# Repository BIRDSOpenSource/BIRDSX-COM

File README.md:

<div align="center">
  
</div> 

<div align="center">
  
</div>

## BIRDSX-COM
Documentaion and CAD files for Antenna Panel in Dragonfly Satellite.

## About the BIRDSX Program:

The Mission Statement of the Project is:

> “The goal of our project is to bring diversity to the space sector and democratize the usage of space.”

The project is led by Kyushu Institute of Technology in Japan and involves students from France, Mexico, Nepal, Thailand, Vietnam, Paraguay and Japan.

Satellite Names: Dragonfly (Japan), 

Stakeholders:  Our stakeholders are Kyushu Institute of Technology (Kyutech) and the Association for Radio Digital Communications (ARDC).

Project duration: 2023-2024

CubeSat: 2U (20x10x10) cm3

Weight: 1.13kg

Launch Date: 21st February 2025

BIRDS-X project is a 2U CubeSat dedicated to amateur radio communication.

## Organisation structure

```bash

```

## Features

## I like this project, can I help you?
You are welcome 🙂

* Give us a star ⭐
* Watch repository to be notified about updates 👀
* If you will find some errors, report them in Issues 🐞
* Try Birds designs on some real computer and let us know how it worked in Discussions. 💬
* We would greatly appreciate if you would also tell others about this ecosystem, it helps us to improve BIRDS Open Source. Thank you!

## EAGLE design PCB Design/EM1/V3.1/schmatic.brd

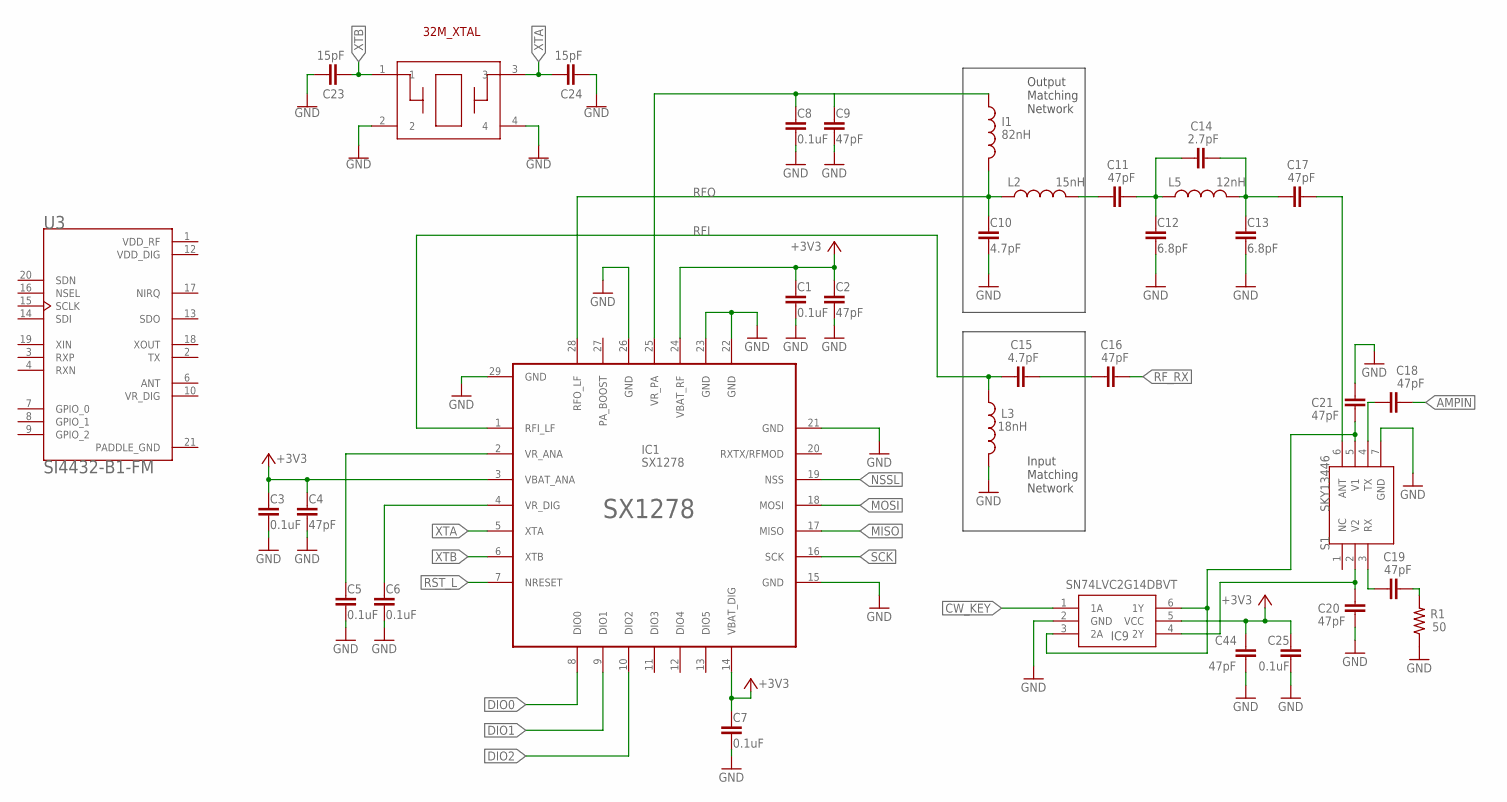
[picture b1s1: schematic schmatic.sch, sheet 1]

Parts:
C1, C3, C5, C6, C7, C8, C25: 0.1uF; M(1005)_US(0402)
C2, C4, C9, C11, C16, C17, C18, C19, C20, C21, C44: 47pF; M(1005)_US(0402)
C10, C15: 4.7pF; M(1005)_US(0402)
C12, C13: 6.8pF; M(1005)_US(0402)
C14: 2.7pF; M(1005)_US(0402)
C23, C24: 15pF; CAP_(M1005)_0402
I1: 82nH; M(1608)_US(0603)
IC1: SX1278
IC9: SN74LVC2G14DBVT; SOT-23-6
L2: 15nH; M(1005)_US(0402)
L3: 18nH; M(1005)_US(0402)
L5: 12nH; M(1005)_US(0402)
Q1: NX2520SA-32MHZ; NX2520SA
R1: 50; M(1608)_US(0603)
S1: SKY13446
U3: SI4432-B1-FM; QFN50P400X400X90-21N

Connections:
+3V1: C5.1, IC1.2 (VR_ANA)
+3V2: C6.1, IC1.4 (VR_DIG)
+3V3: C1.1, C2.1, C3.1, C4.1, C7.1, C25.1, C44.1, IC1.3 (VBAT_ANA), IC1.14 (VBAT_DIG), IC1.24 (VBAT_RF), IC9.5 (VCC); also elsewhere on the board
+3V4: C8.1, C9.1, I1.1, IC1.25 (VR_PA)
AMPIN: C18.2; also elsewhere on the board
CW_KEY: IC9.1 (1A); also elsewhere on the board
DIO0: IC1.8 (DIO0); also elsewhere on the board
DIO1: IC1.9 (DIO1); also elsewhere on the board
DIO2: IC1.10 (DIO2); also elsewhere on the board
GND: C1.2, C2.2, C3.2, C4.2, C5.2, C6.2, C7.2, C8.2, C9.2, C10.2, C12.2, C13.2, C20.1, C21.2, C23.1, C24.2, C25.2, C44.2, IC1.15 (GND), IC1.21 (GND), IC1.22 (GND), IC1.23 (GND), IC1.26 (GND), IC1.29 (GND), IC9.2 (GND), L3.2, Q1.2, Q1.4, R1.1, S1.7 (GND); also elsewhere on the board
MISO: IC1.17 (MISO); also elsewhere on the board
MOSI: IC1.18 (MOSI); also elsewhere on the board
unnamed: C11.1, L2.2
unnamed: C11.2, C12.1, C14.1, L5.1
unnamed: C13.1, C14.2, C17.1, L5.2
unnamed: C17.2, S1.6 (ANT)
unnamed: C15.2, C16.1
unnamed: C18.1, S1.4 (TX)
unnamed: C19.1, S1.3 (RX)
unnamed: C19.2, R1.2
unnamed: C20.2, IC9.4 (2Y), S1.2 (V2)
unnamed: C21.1, IC9.3 (2A), IC9.6 (1Y), S1.5 (V1)
NSSL: IC1.19 (NSS); also elsewhere on the board
RFI: C15.1, IC1.1 (RFI_LF), L3.1
RFO: C10.1, I1.2, IC1.28 (RFO_LF), L2.1
RF_RX: C16.2; also elsewhere on the board
RST_L: IC1.7 (NRESET); also elsewhere on the board
SCK: IC1.16 (SCK); also elsewhere on the board
VDD_DIG: U3.12 (VDD_DIG)
VDD_RF: U3.1 (VDD_RF)
XTA: C24.1, IC1.5 (XTA), Q1.3
XTB: C23.2, IC1.6 (XTB), Q1.1

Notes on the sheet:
Output Matching Network
Input Matching Network
32M_XTAL

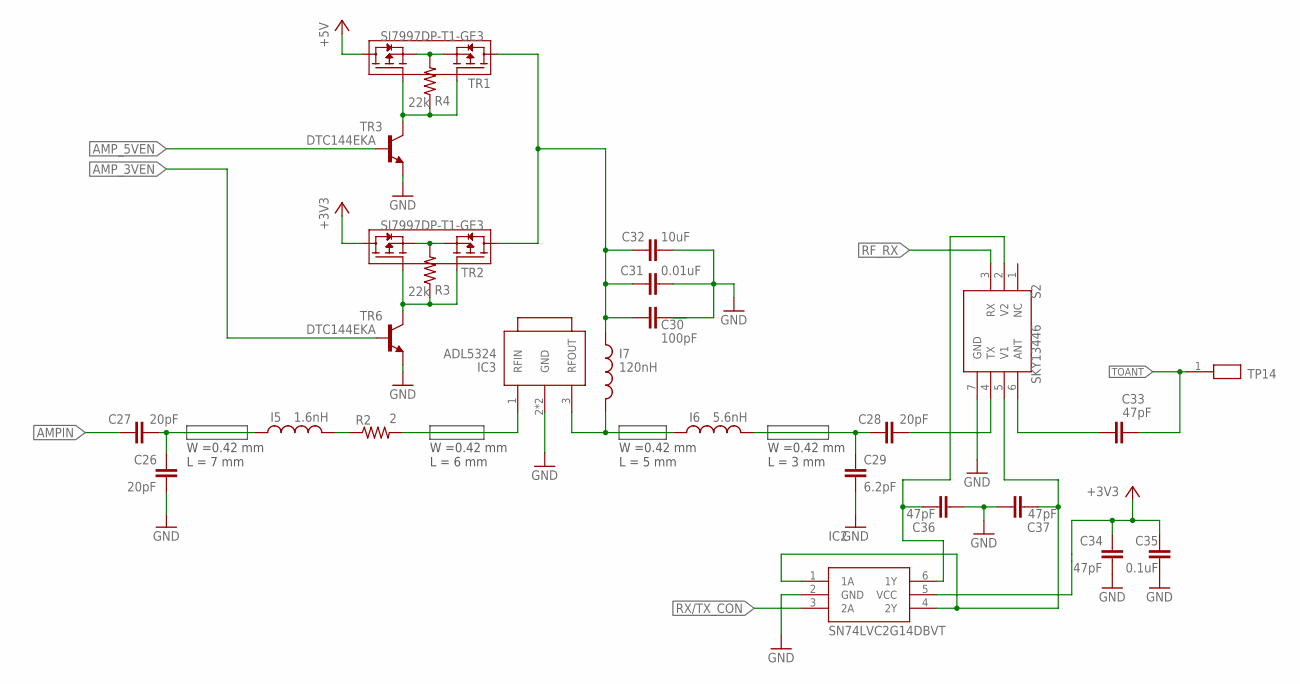
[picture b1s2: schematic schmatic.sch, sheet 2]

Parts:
C26, C27, C28: 20pF; M(1005)_US(0402)
C29: 6.2pF; M(1005)_US(0402)
C30: 100pF; M(1005)_US(0402)
C31: 0.01uF; M(1005)_US(0402)
C32: 10uF; M(1608)_US(0603)
C33, C34, C36, C37: 47pF; M(1005)_US(0402)
C35: 0.1uF; M(1005)_US(0402)
I5: 1.6nH; M(1005)_US(0402)
I6: 5.6nH; M(1005)_US(0402)
I7: 120nH; M(2012)_US(0805)
IC2: SN74LVC2G14DBVT; SOT-23-6
IC3: ADL5324
R2: 2; M(1608)_US(0603)
R3, R4: 22k; M(1608)_US(0603)
S2: SKY13446
TP14: TEST_POINT; TEST_POINT_1.5MM
TR1, TR2: SI7997DP-T1-GE3
TR3, TR6: DTC144EKA; SOT346-R

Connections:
+3V3: C34.1, C35.1, IC2.5 (VCC), TR2.7 (D1), TR2.8 (D1), TR2.10 (D1); also elsewhere on the board
+3V5: C30.1
+5V: TR1.7 (D1), TR1.8 (D1), TR1.10 (D1); also elsewhere on the board
AMPIN: C27.1; also elsewhere on the board
AMPPWR: C30.2, C31.2, C32.1, I7.1, TR1.5 (D2), TR1.6 (D2), TR1.9 (D2), TR2.5 (D2), TR2.6 (D2), TR2.9 (D2)
AMP_3VEN: TR6.2 (B); also elsewhere on the board
AMP_5VEN: TR3.2 (B); also elsewhere on the board
GND: C26.2, C29.2, C31.1, C32.2, C34.2, C35.2, C36.1, C37.2, IC2.2 (GND), IC3.2 (GND), IC3.4 (GND), S2.7 (GND), TR3.1 (E), TR6.1 (E); also elsewhere on the board
unnamed: C26.1, C27.2, I5.1
unnamed: C37.1, IC2.1 (1A), IC2.4 (2Y), S2.5 (V1)
unnamed: I5.2, R2.1
unnamed: IC3.1 (RFIN), R2.2
unnamed: I6.1, I7.2, IC3.3 (RFOUT)
unnamed: C28.1, C29.1, I6.2
unnamed: C28.2, S2.4 (TX)
unnamed: C33.1, S2.6 (ANT)
unnamed: R4.2, TR1.1 (S1), TR1.3 (S2)
unnamed: R3.2, TR2.1 (S1), TR2.3 (S2)
unnamed: C36.2, IC2.6 (1Y), S2.2 (V2)
unnamed: R4.1, TR1.2 (G1), TR1.4 (G2), TR3.3 (C)
unnamed: R3.1, TR2.2 (G1), TR2.4 (G2), TR6.3 (C)
RF_RX: S2.3 (RX); also elsewhere on the board
RX/TX_CON: IC2.3 (2A); also elsewhere on the board
TOANT: C33.2, TP14.1

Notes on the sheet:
W =0.42 mm L = 3 mm
W =0.42 mm L = 5 mm
W =0.42 mm L = 6 mm
W =0.42 mm L = 7 mm

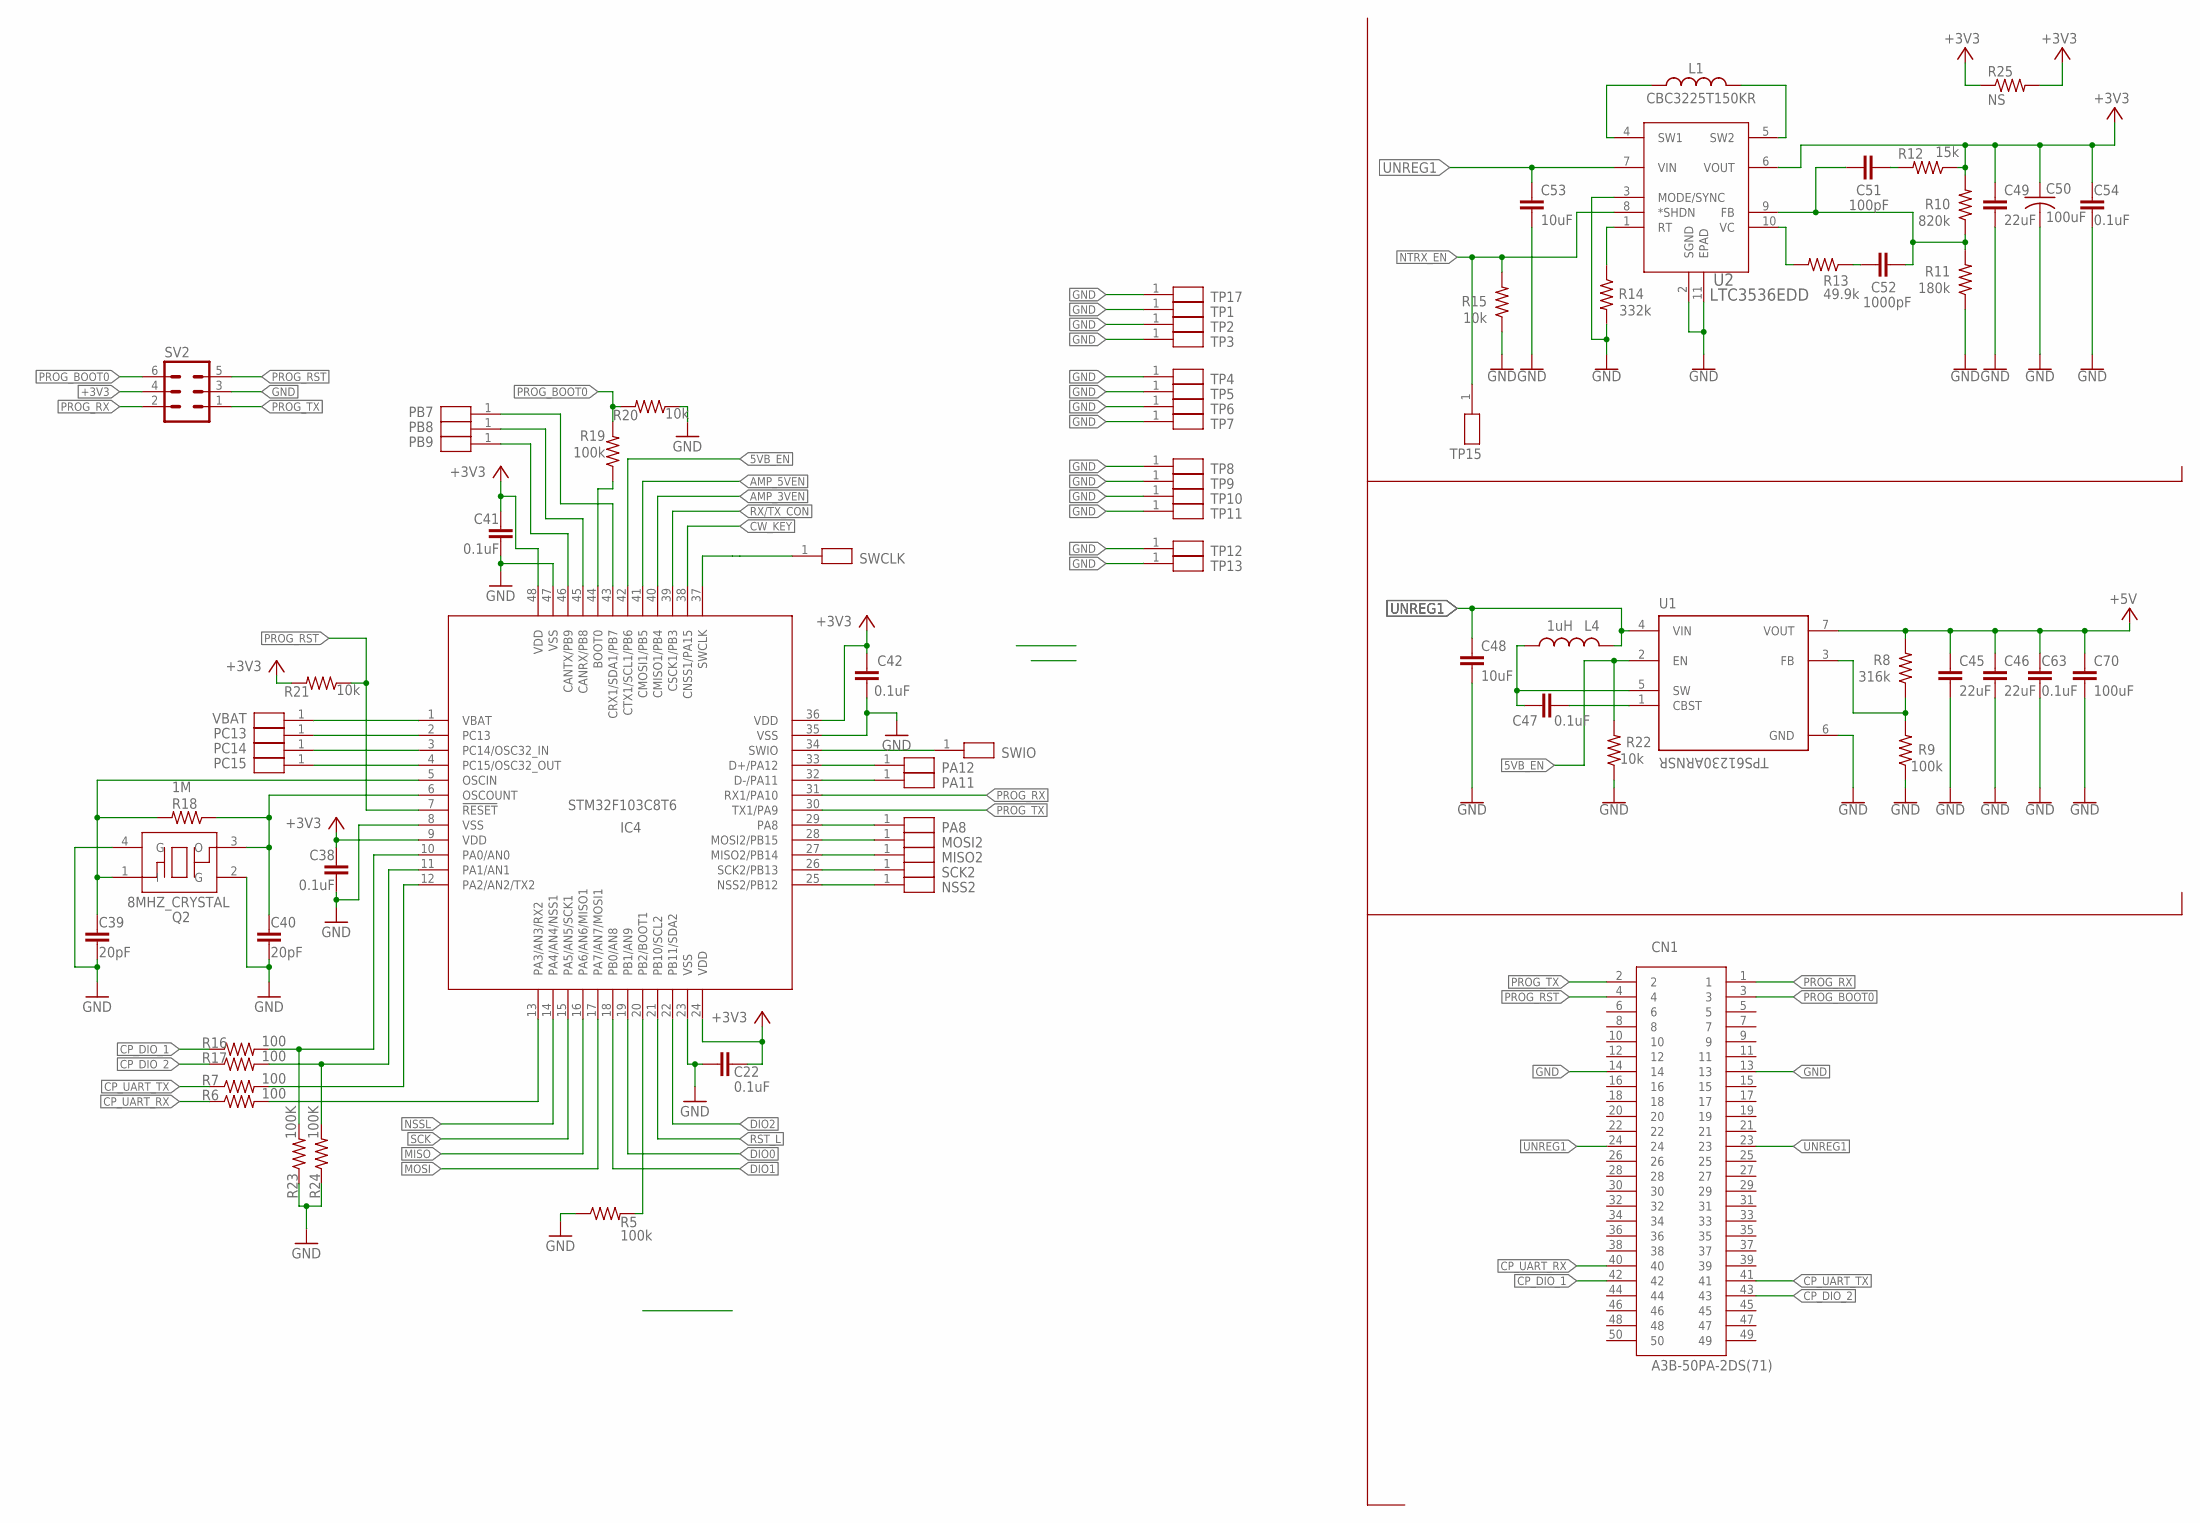
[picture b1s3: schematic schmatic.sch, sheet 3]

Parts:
C22, C38, C41, C42, C47, C54, C63: 0.1uF; M(1005)_US(0402)
C39, C40: 20pF; M(1005)_US(0402)
C45, C46, C49: 22uF; M(1608)_US(0603)
C48, C53: 10uF; M(1608)_US(0603)
C50: 100uF; C1210
C51: 100pF; M(1005)_US(0402)
C52: 1000pF; M(1005)_US(0402)
C70: 100uF; M(2012)_US(0805)
CN1: A3B-50PA-2DS(71)
IC4: STM32F103C8T6
L1: CBC3225T150KR; M(3225)_US(1210)
L4: 1uH; AMDLA3020S-1R5MT
MISO2: TEST_POINT; TEST_POINT_1.5MM
MOSI2: TEST_POINT; TEST_POINT_1.5MM
NSS2: TEST_POINT; TEST_POINT_1.5MM
PA8, PA11, PA12: TEST_POINT; TEST_POINT_1.5MM
PB7, PB8, PB9: TEST_POINT; TEST_POINT_1.5MM
PC13, PC14, PC15: TEST_POINT; TEST_POINT_1.5MM
Q2: 8MHZ_CRYSTAL; ECS-80-18-30B-JEM-TR
R5, R19: 100k; M(1005)_US(0402)
R6, R7, R16, R17: 100; M(1005)_US(0402)
R8: 316k; M(1608)_US(0603)
R9: 100k; M(1608)_US(0603)
R10: 820k; M(1608)_US(0603)
R11: 180k; M(1608)_US(0603)
R12: 15k; M(1608)_US(0603)
R13: 49.9k; M(1608)_US(0603)
R14: 332k; M(1608)_US(0603)
R15, R20, R21, R22: 10k; M(1005)_US(0402)
R18: 1M; M(1608)_US(0603)
R23, R24: 100K; M(1005)_US(0402)
R25: NS; M(2012)_US(0805)
SCK2: TEST_POINT; TEST_POINT_1.5MM
SV2: MA03-2
SWCLK: TEST_POINT; TEST_POINT_1.5MM
SWIO: TEST_POINT; TEST_POINT_1.5MM
TP1, TP2, TP3, TP4, TP5, TP6, TP7, TP8, TP9, TP10, TP11, TP12, TP13, TP15, TP17: TEST_POINT; TEST_POINT_1.5MM
U1: TPS61230ARNSR; IC_TPS61230ARNSR
U2: LTC3536EDD; DFN-10_DD
VBAT: TEST_POINT; TEST_POINT_1.5MM

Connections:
5VB_EN: IC4.42 (CTX1/SCL1/PB6), R22.2, U1.2 (EN)
+3V3: C22.1, C38.1, C41.1, C42.1, C49.1, C50.1, C54.1, IC4.9 (VDD), IC4.24 (VDD), IC4.36 (VDD), IC4.48 (VDD), R10.2, R12.1, R21.2, R25.1, R25.2, SV2.4, U2.6 (VOUT); also elsewhere on the board
+5V: C45.1, C46.1, C63.1, C70.1, R8.2, U1.7 (VOUT); also elsewhere on the board
AMP_3VEN: IC4.40 (CMISO1/PB4); also elsewhere on the board
AMP_5VEN: IC4.41 (CMOSI1/PB5); also elsewhere on the board
CP_DIO_1: CN1.42, R16.1
CP_DIO_2: CN1.43, R17.1
CP_UART_RX: CN1.40, R6.1
CP_UART_TX: CN1.41, R7.1
CW_KEY: IC4.38 (CNSS1/PA15); also elsewhere on the board
C_UART_RX: IC4.13 (PA3/AN3/RX2), R6.2
C_UART_TX: IC4.12 (PA2/AN2/TX2), R7.2
DIO0: IC4.19 (PB1/AN9); also elsewhere on the board
DIO1: IC4.18 (PB0/AN8); also elsewhere on the board
DIO2: IC4.22 (PB11/SDA2); also elsewhere on the board
GND: C22.2, C38.2, C39.2, C40.2, C41.2, C42.2, C45.2, C46.2, C48.2, C49.2, C50.2, C53.2, C54.2, C63.2, C70.2, CN1.13, CN1.14, IC4.8 (VSS), IC4.23 (VSS), IC4.35 (VSS), IC4.47 (VSS), Q2.2 (G), Q2.4 (G), R5.1, R9.1, R11.1, R14.2, R15.1, R20.1, R22.1, R23.1, R24.1, SV2.3, TP1.1, TP2.1, TP3.1, TP4.1, TP5.1, TP6.1, TP7.1, TP8.1, TP9.1, TP10.1, TP11.1, TP12.1, TP13.1, TP17.1, U1.6 (GND), U2.2 (SGND), U2.3 (MODE/SYNC), U2.11 (EPAD); also elsewhere on the board
MISO: IC4.16 (PA6/AN6/MISO1); also elsewhere on the board
MOSI: IC4.17 (PA7/AN7/MOSI1); also elsewhere on the board
unnamed: IC4.10 (PA0/AN0), R16.2, R23.2
unnamed: IC4.20 (PB2/BOOT1), R5.2
unnamed: IC4.11 (PA1/AN1), R17.2, R24.2
unnamed: C39.1, IC4.5 (OSCIN), Q2.1 (I), R18.2
unnamed: C40.1, IC4.6 (OSCOUNT), Q2.3 (O), R18.1
unnamed: L1.1, U2.4 (SW1)
unnamed: R8.1, R9.2, U1.3 (FB)
unnamed: C47.1, L4.1, U1.5 (SW)
unnamed: L1.2, U2.5 (SW2)
unnamed: C47.2, U1.1 (CBST)
unnamed: IC4.1 (VBAT), VBAT.1
unnamed: C51.2, R12.2
unnamed: C51.1, C52.2, R10.1, R11.2, U2.9 (FB)
unnamed: IC4.44 (BOOT0), R19.1
unnamed: C52.1, R13.1
unnamed: R13.2, U2.10 (VC)
unnamed: R14.1, U2.1 (RT)
unnamed: IC4.4 (PC15/OSC32_OUT), PC15.1
unnamed: IC4.3 (PC14/OSC32_IN), PC14.1
unnamed: IC4.2 (PC13), PC13.1
unnamed: IC4.27 (MISO2/PB14), MISO2.1
unnamed: IC4.28 (MOSI2/PB15), MOSI2.1
unnamed: IC4.33 (D+/PA12), PA12.1
unnamed: IC4.32 (D-/PA11), PA11.1
unnamed: IC4.29 (PA8), PA8.1
unnamed: IC4.26 (SCK2/PB13), SCK2.1
unnamed: IC4.25 (NSS2/PB12), NSS2.1
NSSL: IC4.14 (PA4/AN4/NSS1); also elsewhere on the board
NTRX_EN: R15.2, TP15.1, U2.8 (*SHDN)
PB7: IC4.43 (CRX1/SDA1/PB7), PB7.1
PB8: IC4.45 (CANRX/PB8), PB8.1
PB9: IC4.46 (CANTX/PB9), PB9.1
PROG_BOOT0: CN1.3, R19.2, R20.2, SV2.6
PROG_RST: CN1.4, IC4.7 (!RESET), R21.1, SV2.5
PROG_RX: CN1.1, IC4.31 (RX1/PA10), SV2.2
PROG_TX: CN1.2, IC4.30 (TX1/PA9), SV2.1
RST_L: IC4.21 (PB10/SCL2); also elsewhere on the board
RX/TX_CON: IC4.39 (CSCK1/PB3); also elsewhere on the board
SCK: IC4.15 (PA5/AN5/SCK1); also elsewhere on the board
SWCLK: IC4.37 (SWCLK), SWCLK.1
SWIO: IC4.34 (SWIO), SWIO.1
UNREG1: C48.1, C53.1, CN1.23, CN1.24, L4.2, U1.4 (VIN), U2.7 (VIN)

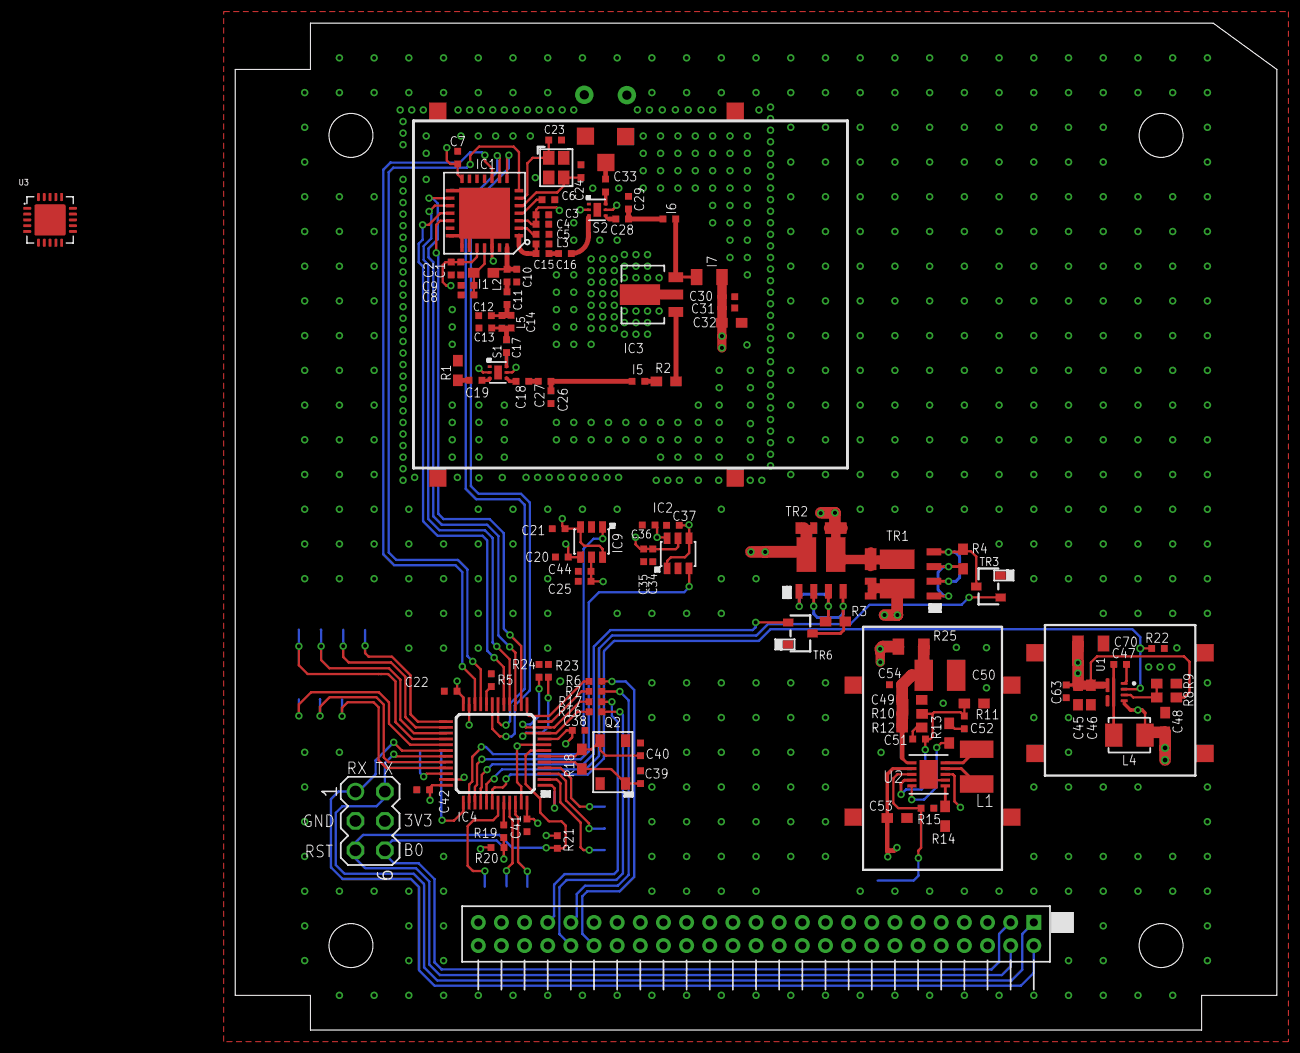
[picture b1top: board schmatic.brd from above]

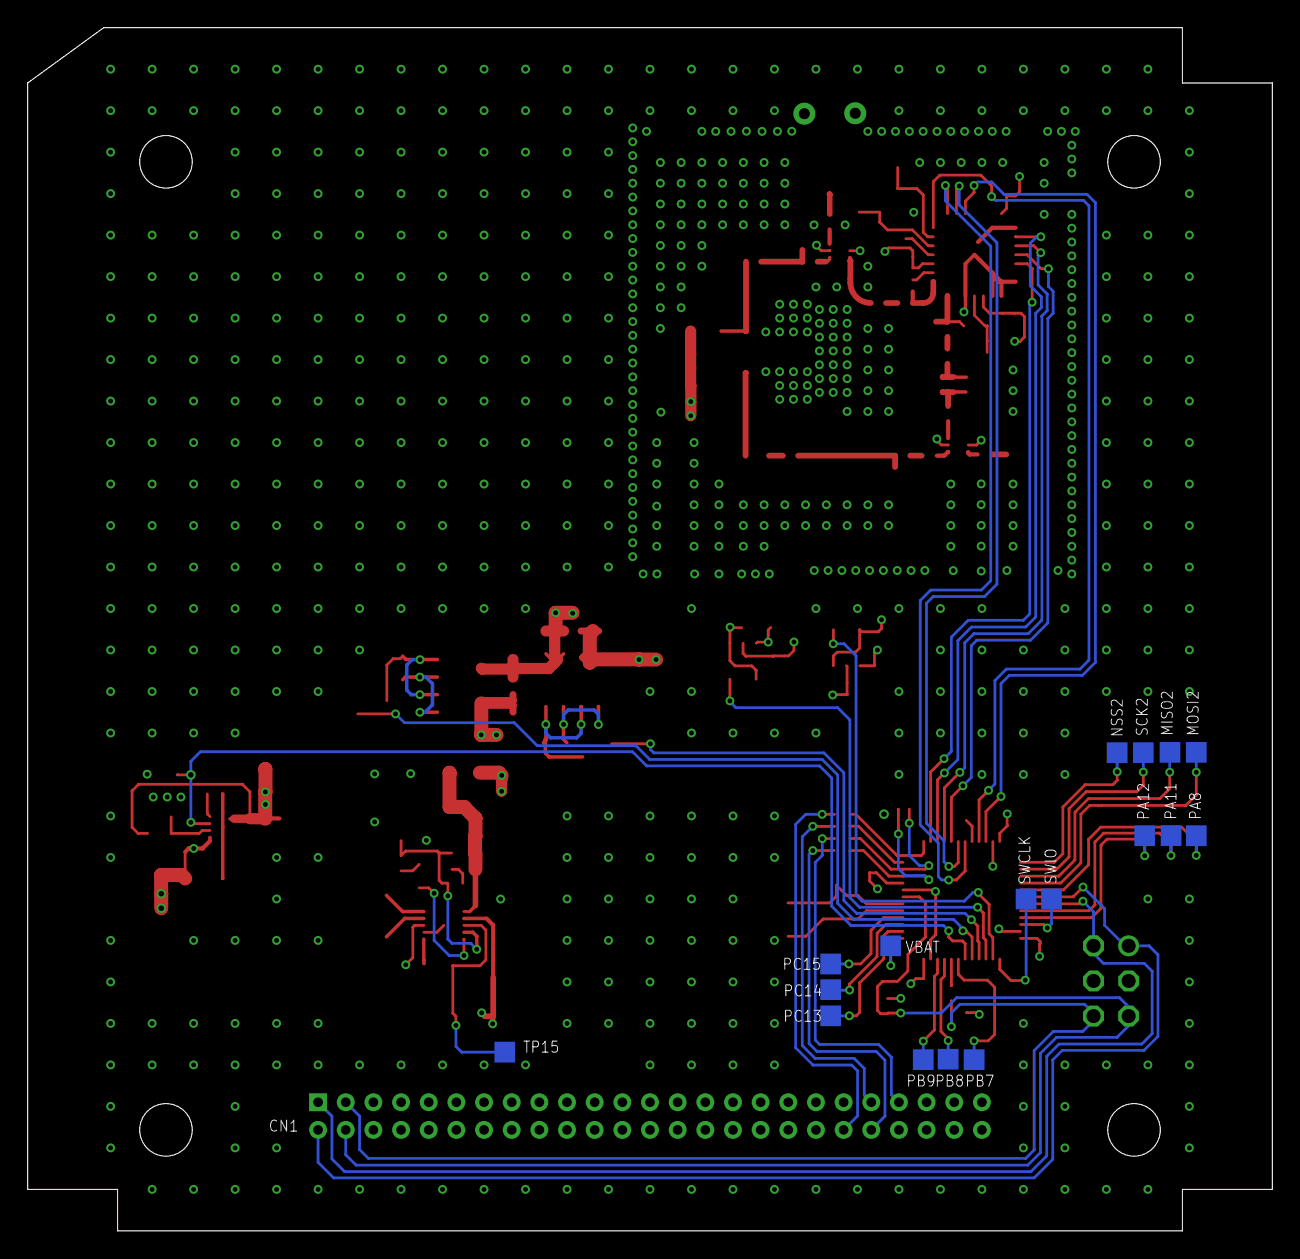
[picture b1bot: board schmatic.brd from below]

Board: 4 copper layers, 90.0 x 87.0 mm, 139 parts (18 on the bottom side), 94 nets.

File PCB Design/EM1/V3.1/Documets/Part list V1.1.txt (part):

Partlist

Exported from schmatic.brd at 20/02/2023 10:19

EAGLE Version 9.6.2 Copyright (c) 1988-2020 Autodesk, Inc.

Assembly variant: 

Part     Value            Package          Library          Position (mm)         Orientation

C1       0.1uF            M(1005)_US(0402) Tharindu_lib     (19.49 65.8)          R270
C2       47pF             M(1005)_US(0402) Tharindu_lib     (18.66 65.8)          R270
C3       0.1uF            M(1005)_US(0402) Tharindu_lib     (26.54 70.44)         R0
C4       47pF             M(1005)_US(0402) Tharindu_lib     (26.54 69.63)         R0
C5       0.1uF            M(1005)_US(0402) Tharindu_lib     (26.55 68.76)         R0
C6       0.1uF            M(1005)_US(0402) Tharindu_lib     (27.06 71.74)         R0
C7       0.1uF            M(1005)_US(0402) Tharindu_lib     (19.22 75.38)         R90
C8       0.1uF            M(1005)_US(0402) Tharindu_lib     (20.07 63.52)         R180
C9       47pF             M(1005)_US(0402) Tharindu_lib     (20.07 64.34)         R180
C10      4.7pF            M(1005)_US(0402) Tharindu_lib     (24.32 65.19)         R270
C11      47pF             M(1005)_US(0402) Tharindu_lib     (23.49 63.24)         R270
C12      6.8pF            M(1005)_US(0402) Tharindu_lib     (21.58 61.73)         R180
C13      6.8pF            M(1005)_US(0402) Tharindu_lib     (21.61 60.66)         R180
C14      2.7pF            M(1005)_US(0402) Tharindu_lib     (23.84 61.2)          R270
C15      4.7pF            M(1005)_US(0402) Tharindu_lib     (26.55 67.09)         R0
C16      47pF             M(1005)_US(0402) Tharindu_lib     (28.49 67.09)         R0
C17      47pF             M(1005)_US(0402) Tharindu_lib     (23.44 59.09)         R270
C18      47pF             M(1005)_US(0402) Tharindu_lib     (24.81 56.05)         R0
C19      47pF             M(1005)_US(0402) Tharindu_lib     (20.76 56.14)         R180
C20      47pF             M(1005)_US(0402) Tharindu_lib     (28.22 40.87)         R0
C21      47pF             M(1005)_US(0402) Tharindu_lib     (27.945 43.32)        R180
C22      0.1uF            M(1005)_US(0402) Tharindu_lib     (18.62 29.28)         R180
C23      15pF             CAP_(M1005)_0402 Tharindu         (27.64 76.9)          R180
C24      15pF             CAP_(M1005)_0402 Tharindu         (29.87 74.21)         R90
C25      0.1uF            M(1005)_US(0402) Tharindu_lib     (30.19 38.77)         R180
C26      20pF             M(1005)_US(0402) Tharindu_lib     (27.28 54.68)         R270
C27      20pF             M(1005)_US(0402) Tharindu_lib     (26.73 56.05)         R0
C28      20pF             M(1005)_US(0402) Tharindu_lib     (33.43 70.08)         R180
C29      6.2pF            M(1005)_US(0402) Tharindu_lib     (33.98 71.48)         R90
C30      100pF            M(1005)_US(0402) Tharindu_lib     (42.61 63.37)         R180
C31      10000pF          M(1608)_US(0603) Tharindu_lib     (42.9 62.26)          R0
C32      10uF             M(1608)_US(0603) Tharindu_lib     (42.9 61.11)          R0
C33      47pF             M(1005)_US(0402) Tharindu_lib     (32 72.97)            R90
C34      47pF             M(1005)_US(0402) Tharindu_lib     (36.08 41.02)         R270
C35      0.1uF            M(1005)_US(0402) Tharindu_lib     (35.29 41.02)         R270
C36      47pF             M(1005)_US(0402) Tharindu_lib     (35.72 43.63)         R0
C37      47pF             M(1005)_US(0402) Tharindu_lib     (37.82 43.61)         R180
C38      0.1uF            M(1005)_US(0402) Tharindu_lib     (29.67 25.89)         R0
C39      20pF             M(1005)_US(0402) Tharindu_lib     (35.02 22.23)         R90
C40      20pF             M(1005)_US(0402) Tharindu_lib     (35.02 24.59)         R270
C41      0.1uF            M(1005)_US(0402) Tharindu_lib     (25.2 17.69)          R270
C42      0.1uF            M(1005)_US(0402) Tharindu_lib     (16.24 20.76)         R180
C44      47pF             M(1005)_US(0402) Tharindu_lib     (30.2 39.63)          R180
C45      22uF             M(1608)_US(0603) Tharindu_lib     (72.82 28.95)         R270
C46      22uF             M(1608)_US(0603) Tharindu_lib     (73.93 28.95)         R270
C47      10nF             M(1608)_US(0603) Tharindu_lib     (76.78 31.37)         R180
C48      10uF             M(1608)_US(0603) Tharindu_lib     (80.35 26.58)         R90
C49      22uF             M(1608)_US(0603) Tharindu_lib     (58.3 29.03)          R0
C50      100uF            M(2012)_US(0805) Tharindu_lib     (58.55 30.48)         R0
C51      100pF            M(1005)_US(0402) Tharindu_lib     (58.92 25.64)         R180
C52      1000pF           M(1005)_US(0402) Tharindu_lib     (62.46 27.55)         R90
C53      10uF             M(1608)_US(0603) Tharindu_lib     (57.03 19.11)         R0
C54      0.1uF            M(1005)_US(0402) Tharindu_lib     (58.85 31.73)         R0
C63      0.1uF            M(1005)_US(0402) Tharindu_lib     (71.8 29.27)          R270
C70      100uF            M(2012)_US(0805) Tharindu_lib     (73.92 33.4)          R0
CN1      A3B-50PA-2DS(71) A3B-50PA-2DS(71) Tharindu1        (69 7.3)              MR0
I1       82nH             M(1608)_US(0603) Tharindu_lib     (21.46 65.43)         R0
I5       1.6nH            M(1005)_US(0402) Tharindu_lib     (34.84 56.05)         R0
I6       5.6nH            M(1005)_US(0402) Tharindu_lib     (37.51 70.08)         R180
I7       120nH            M(2012)_US(0805) Tharindu_lib     (40.96 65.06)         R180
IC1      SX1278           SX1278           Tharindu         (21.54 70.58)         R180
IC2      SN74LVC2G14DBVT  SOT-23-6         Tharindu         (38.27 41.19)         R0
IC3      ADL5324          ADL5324          Tharindu         (38.07 63.55)         R90
IC4      STM32F103C8T6    STM32F103C8T6    Tharindu         (22.46 23.9)          R180
IC9      SN74LVC2G14DBVT  SOT-23-6         Tharindu         (30.79 42.16)         R180
L1       CBC3225T150KR    M(3225)_US(1210) Tharindu_lib     (63.89 23.26)         R90
L2       15nH             M(1005)_US(0402) Tharindu_lib     (23.49 65.19)         R270
L3       18nH             M(1005)_US(0402) Tharindu_lib     (26.55 67.92)         R0
L4       1uH              AMDLA3020S-1R5MT Tharindu         (77.26 25.98)         R0
L5       12nH             M(1005)_US(0402) Tharindu_lib     (23.05 61.19)         R270
MISO2    TEST_POINT       TEST_POINT_1.5MM Tharindu         (7.4 34.6)            MR90
MOSI2    TEST_POINT       TEST_POINT_1.5MM Tharindu         (5.5 34.6)            MR90
NSS2     TEST_POINT       TEST_POINT_1.5MM Tharindu         (11.22 34.57)         MR0
PA8      TEST_POINT       TEST_POINT_1.5MM Tharindu         (5.5 28.57)           MR90
PA11     TEST_POINT       TEST_POINT_1.5MM Tharindu         (7.32 28.58)          MR90
PA12     TEST_POINT       TEST_POINT_1.5MM Tharindu         (9.23 28.57)          MR90
PB7      TEST_POINT       TEST_POINT_1.5MM Tharindu         (21.56 12.38)         MR0
PB8      TEST_POINT       TEST_POINT_1.5MM Tharindu         (23.44 12.41)         MR0
PB9      TEST_POINT       TEST_POINT_1.5MM Tharindu         (25.24 12.38)         MR0
PC13     TEST_POINT       TEST_POINT_1.5MM Tharindu         (31.93 15.55)         MR270
PC14     TEST_POINT       TEST_POINT_1.5MM Tharindu         (31.93 17.44)         MR0
PC15     TEST_POINT       TEST_POINT_1.5MM Tharindu         (31.93 19.3)          MR90
Q1       NX2520SA-32MHZ   NX2520SA         Tharindu         (27.74 74.51)         R270
Q2       XTAL             16MHZ_2-SMD      Tharindu         (32.57 23.4)          R270
R1       50               M(1608)_US(0603) Tharindu_lib     (19.24 56.99)         R270
R2       2                M(1608)_US(0603) Tharindu_lib     (37.24 56.05)         R0
R3       22k              M(1608)_US(0603) Tharindu_lib     (51.86 35.3)          R180
R4       22k              M(1608)_US(0603) Tharindu_lib     (62.88 40.7)          R270
R5       100k             M(1005)_US(0402) Tharindu_lib     (22.13 30.23)         R270
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
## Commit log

2024-11-04 Create PCB Design
2024-11-17 Create LinkBudget

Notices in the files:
parts and their libraries:
SparkFun-PowerSymbols: Licensing: Creative Commons ShareAlike 4.0 International - https://creativecommons.org/licenses/by-sa/4.0
